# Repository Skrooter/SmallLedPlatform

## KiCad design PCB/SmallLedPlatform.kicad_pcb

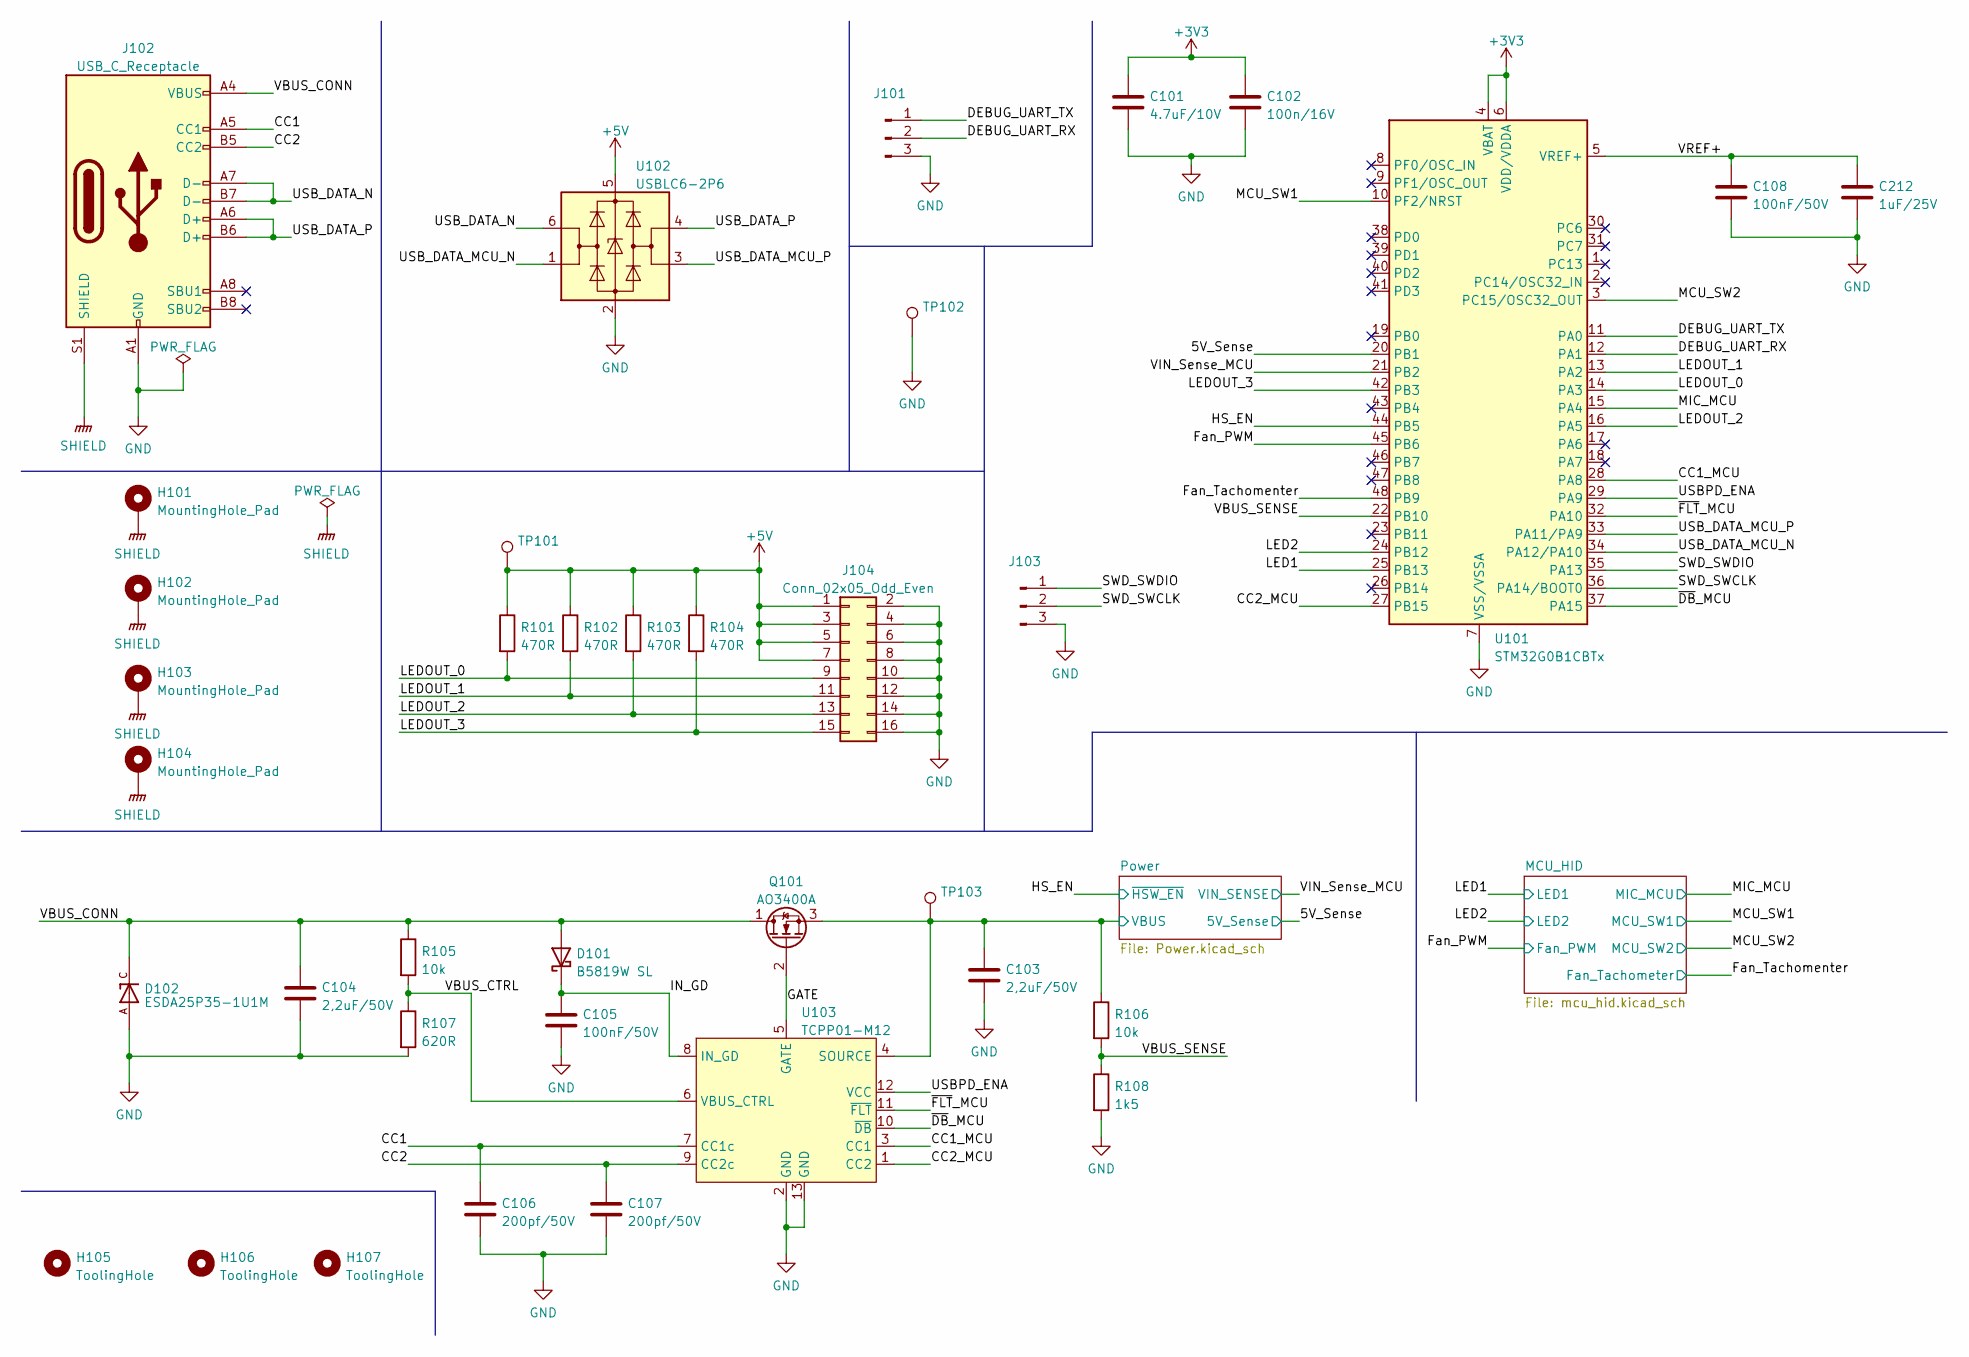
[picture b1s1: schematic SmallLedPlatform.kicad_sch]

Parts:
C101: 4.7uF/10V; C_0402_1005Metric; LCSC C23733
C102: 100n/16V; C_0402_1005Metric; LCSC C1525
C103, C104: 2,2uF/50V; C_0805_2012Metric; LCSC C49217
C105, C108: 100nF/50V; C_0402_1005Metric; LCSC C307331
C106, C107: 200pf/50V; C_0603_1608Metric; LCSC C1600
C212: 1uF/25V; C_0402_1005Metric; LCSC C52923
D101: B5819W SL; D_SOD-123; LCSC C8598
D102: ESDA25P35-1U1M; TVS_ESDA25P35-1U1M; PARTREV 2; LCSC C1974707
H101, H102, H103, H104: MountingHole_Pad; MountingHole_3.2mm_M3_Pad_Via
H105, H106, H107: ToolingHole; JLC_toolinghole
J101, J103: Conn_01x03_Male; PinHeader_1x03_P2.54mm_Vertical; LCSC C49257
J102: USB_C_Receptacle; USB_C_Receptacle_GCT_USB4105-xx-A_16P_TopMnt_Horizontal; LCSC C165948
J104: Conn_02x05_Odd_Even; PinHeader_2x08_P2.54mm_Horizontal; LCSC C68234
Q101: AO3400A; SOT-23; LCSC C20917
R101, R102, R103, R104: 470R; R_0402_1005Metric; LCSC C25117
R105, R106: 10k; R_0402_1005Metric; LCSC C25744
R107: 620R; R_0603_1608Metric; LCSC C23220
R108: 1k5; R_0402_1005Metric; LCSC C25867
TP101, TP102, TP103: TestPoint; TestPoint_Keystone_5000-5004_Miniature; LCSC C5199798
U101: STM32G0B1CBTx; LQFP-48_7x7mm_P0.5mm; LCSC C2847904
U102: USBLC6-2P6; SOT-666; LCSC C2827693
U103: TCPP01-M12; QFN-12-1EP_3x3mm_P0.5mm_EP1.6x1.6mm; LCSC C1121848

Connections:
+3V3: C101.1, C102.1, U101.4 (VBAT), U101.6 (VDD/VDDA); also elsewhere on the board
+5V: J104.1, J104.3, J104.5, J104.7, R101.1, R102.1, R103.1, R104.1, TP101.1, U102.5 (VBUS); also elsewhere on the board
/5V_Sense: U101.20 (PB1); also elsewhere on the board
/CC1: C106.1, J102.A5 (CC1), U103.7 (CC1c)
/CC1_MCU: U101.28 (PA8), U103.3 (CC1)
/CC2: C107.1, J102.B5 (CC2), U103.9 (CC2c)
/CC2_MCU: U101.27 (PB15), U103.1 (CC2)
/DEBUG_UART_RX: J101.2, U101.12 (PA1)
/DEBUG_UART_TX: J101.1, U101.11 (PA0)
/Fan_PWM: U101.45 (PB6); also elsewhere on the board
/Fan_Tachomenter: U101.48 (PB9); also elsewhere on the board
/GATE: Q101.2 (G), U103.5 (GATE)
/HS_EN: U101.44 (PB5); also elsewhere on the board
/IN_GD: C105.1, D101.1 (K), U103.8 (IN_GD)
/LED1: U101.25 (PB13); also elsewhere on the board
/LED2: U101.24 (PB12); also elsewhere on the board
/LEDOUT_0: J104.9, R101.2, U101.14 (PA3)
/LEDOUT_1: J104.11, R102.2, U101.13 (PA2)
/LEDOUT_2: J104.13, R103.2, U101.16 (PA5)
/LEDOUT_3: J104.15, R104.2, U101.42 (PB3)
/MCU_SW1: U101.10 (PF2/NRST); also elsewhere on the board
/MCU_SW2: U101.3 (PC15/OSC32_OUT); also elsewhere on the board
/MIC_MCU: U101.15 (PA4); also elsewhere on the board
/SWD_SWCLK: J103.2, U101.36 (PA14/BOOT0)
/SWD_SWDIO: J103.1, U101.35 (PA13)
/USBPD_ENA: U101.29 (PA9), U103.12 (VCC)
/USB_DATA_MCU_N: U101.34 (PA12/PA10), U102.1 (I/O1)
/USB_DATA_MCU_P: U101.33 (PA11/PA9), U102.3 (I/O2)
/USB_DATA_N: J102.A7 (D-), J102.B7 (D-), U102.6 (I/O1)
/USB_DATA_P: J102.A6 (D+), J102.B6 (D+), U102.4 (I/O2)
/VBUS_CONN: C104.1, D101.2 (A), D102.C, J102.A4 (VBUS), J102.A9 (VBUS), J102.B4 (VBUS), J102.B9 (VBUS), Q101.1 (D), R105.1
/VBUS_CTRL: R105.2, R107.1, U103.6 (VBUS_CTRL)
/VBUS_SENSE: R106.2, R108.1, U101.22 (PB10)
/VIN_Sense_MCU: U101.21 (PB2); also elsewhere on the board
/~DB_MCU: U101.37 (PA15), U103.10 (~DB)
/~FLT_MCU: U101.32 (PA10), U103.11 (~FLT)
GND: C101.2, C102.2, C103.2, C104.2, C105.2, C106.2, C107.2, C108.2, C212.2, D102.A, J101.3, J102.A1 (GND), J102.A12 (GND), J102.B1 (GND), J102.B12 (GND), J103.3, J104.2, J104.4, J104.6, J104.8, J104.10, J104.12, J104.14, J104.16, R107.2, R108.2, TP102.1, U101.7 (VSS/VSSA), U102.2 (GND), U103.2 (GND), U103.13 (GND); also elsewhere on the board
IN: C103.1, Q101.3 (S), R106.1, TP103.1, U103.4 (SOURCE); also elsewhere on the board
SHIELD: H101.1, H102.1, H103.1, H104.1, J102.S1 (SHIELD)

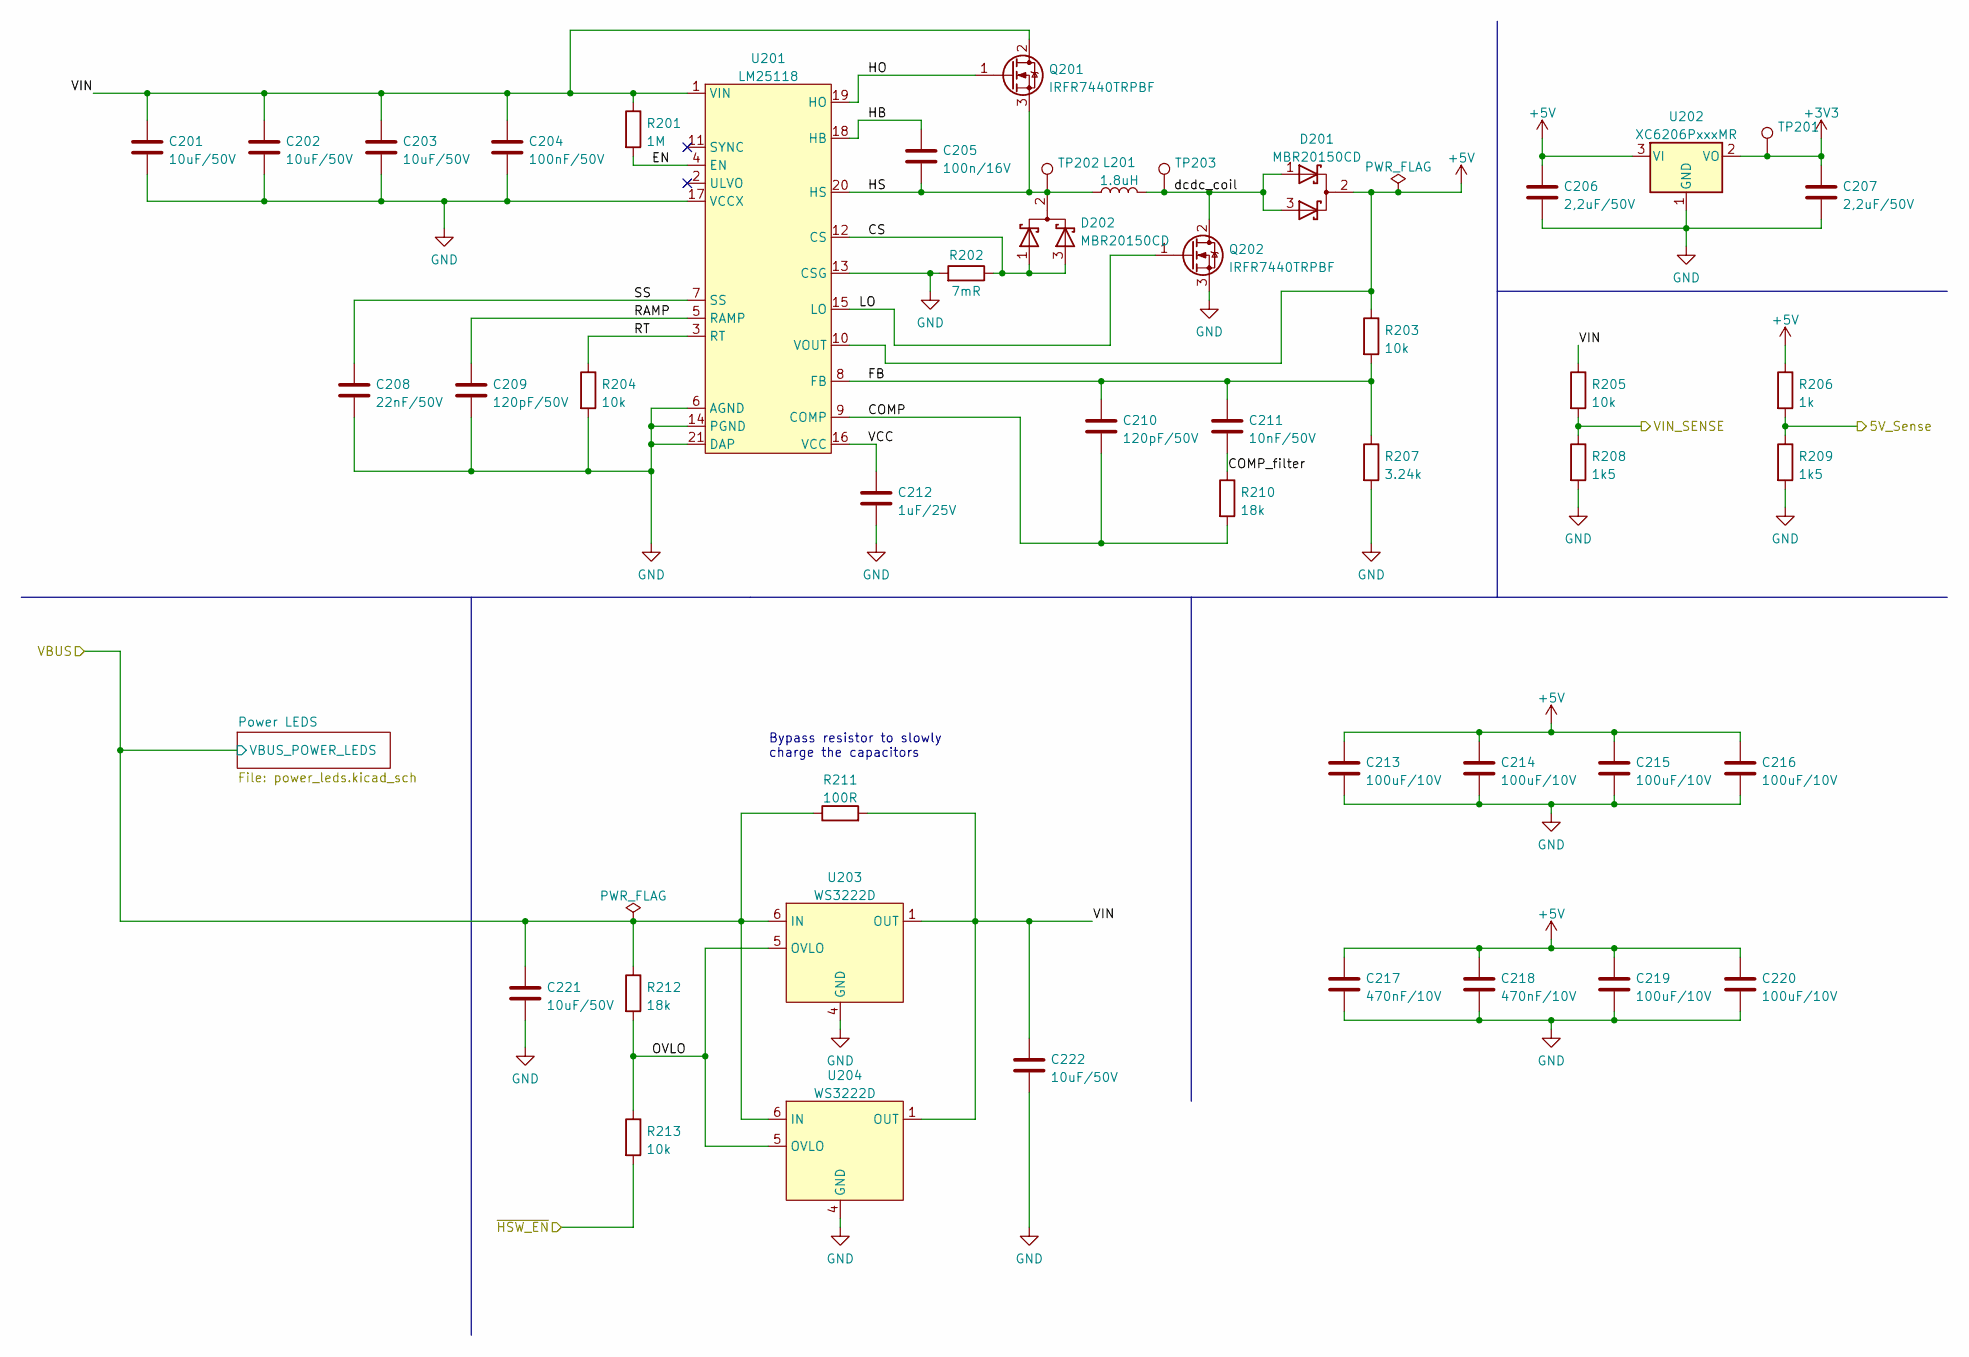
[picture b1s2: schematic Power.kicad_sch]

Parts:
C201, C202, C203, C221, C222: 10uF/50V; C_0805_2012Metric; LCSC C440198
C204: 100nF/50V; C_0402_1005Metric; LCSC C307331
C205: 100n/16V; C_0402_1005Metric; LCSC C1525
C206, C207: 2,2uF/50V; C_0805_2012Metric; LCSC C49217
C208: 22nF/50V; C_0402_1005Metric; LCSC C1532
C209, C210: 120pF/50V; C_0402_1005Metric; LCSC C312114
C211: 10nF/50V; C_0402_1005Metric; LCSC C15195
C212: 1uF/25V; C_0402_1005Metric; LCSC C52923
C213, C214, C215, C216, C219, C220: 100uF/10V; C_1206_3216Metric; LCSC C312983
C217, C218: 470nF/10V; C_0402_1005Metric; LCSC C47339
D201, D202: MBR20150CD; TO-252-2; LCSC C698783
L201: 1.8uH; L_12x12mm_H8mm; LCSC C718301
Q201, Q202: IRFR7440TRPBF; TO-252-2; LCSC C97244
R201: 1M; R_0402_1005Metric; LCSC C26083
R202: 7mR; R_2512_6332Metric; LCSC C728341
R203, R204, R205, R213: 10k; R_0402_1005Metric; LCSC C25744
R206: 1k; R_0402_1005Metric; LCSC C11702
R207: 3.24k; R_0402_1005Metric; LCSC C25890
R208, R209: 1k5; R_0402_1005Metric; LCSC C25867
R210, R212: 18k; R_0402_1005Metric; LCSC C25762
R211: 100R; R_1206_3216Metric; LCSC C17901
TP201, TP202, TP203: TestPoint; TestPoint_Keystone_5000-5004_Miniature; LCSC C5199798
U201: LM25118; HTSSOP-20-1EP_4.4x6.5mm_P0.65mm_EP3.4x6.5mm_Mask2.75x3.43mm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; LCSC C470962
U202: XC6206PxxxMR; SOT-23-3; LCSC C5446
U203, U204: WS3222D; WDFN-8-1EP_2x2mm_P0.5mm_EP0.8x1.2mm; LCSC C239703

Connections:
+3V3: C207.1, TP201.1, U202.2 (VO); also elsewhere on the board
+5V: C206.1, C213.1, C214.1, C215.1, C216.1, C217.1, C218.1, C219.1, C220.1, D201.2 (A), R203.1, R206.1, U201.10 (VOUT), U202.3 (VI); also elsewhere on the board
/5V_Sense: R206.2, R209.1; also elsewhere on the board
/HS_EN: R213.2; also elsewhere on the board
/Power/COMP: C210.2, R210.2, U201.9 (COMP)
/Power/COMP_filter: C211.2, R210.1
/Power/CS: D202.1 (K), D202.3 (K), R202.1, U201.12 (CS)
/Power/EN: R201.2, U201.4 (EN)
/Power/FB: C210.1, C211.1, R203.2, R207.1, U201.8 (FB)
/Power/HB: C205.1, U201.18 (HB)
/Power/HO: Q201.1 (G), U201.19 (HO)
/Power/HS: C205.2, D202.2 (A), L201.1, Q201.3 (S), TP202.1, U201.20 (HS)
/Power/LO: Q202.1 (G), U201.15 (LO)
/Power/OVLO: R212.2, R213.1, U203.5 (OVLO), U204.5 (OVLO)
/Power/RAMP: C209.1, U201.5 (RAMP)
/Power/RT: R204.1, U201.3 (RT)
/Power/SS: C208.1, U201.7 (SS)
/Power/VIN: C201.1, C202.1, C203.1, C204.1, C222.1, Q201.2 (D), R201.1, R205.1, R211.2, U201.1 (VIN), U203.1 (OUT), U203.2 (OUT), U203.3 (OUT), U204.1 (OUT), U204.2 (OUT), U204.3 (OUT)
/Power/dcdc_coil: D201.1 (K), D201.3 (K), L201.2, Q202.2 (D), TP203.1
/VIN_Sense_MCU: R205.2, R208.1; also elsewhere on the board
GND: C201.2, C202.2, C203.2, C204.2, C206.2, C207.2, C208.2, C209.2, C212.2, C213.2, C214.2, C215.2, C216.2, C217.2, C218.2, C219.2, C220.2, C221.2, C222.2, Q202.3 (S), R202.2, R204.2, R207.2, R208.2, R209.2, U201.6 (AGND), U201.13 (CSG), U201.14 (PGND), U201.17 (VCCX), U201.21 (DAP), U202.1 (GND), U203.4 (GND), U203.9 (GND), U204.4 (GND), U204.9 (GND); also elsewhere on the board
IN: C221.1, R211.1, R212.1, U203.6 (IN), U203.7 (IN), U203.8 (IN), U204.6 (IN), U204.7 (IN), U204.8 (IN); also elsewhere on the board

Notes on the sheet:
Bypass resistor to slowly charge the capacitors

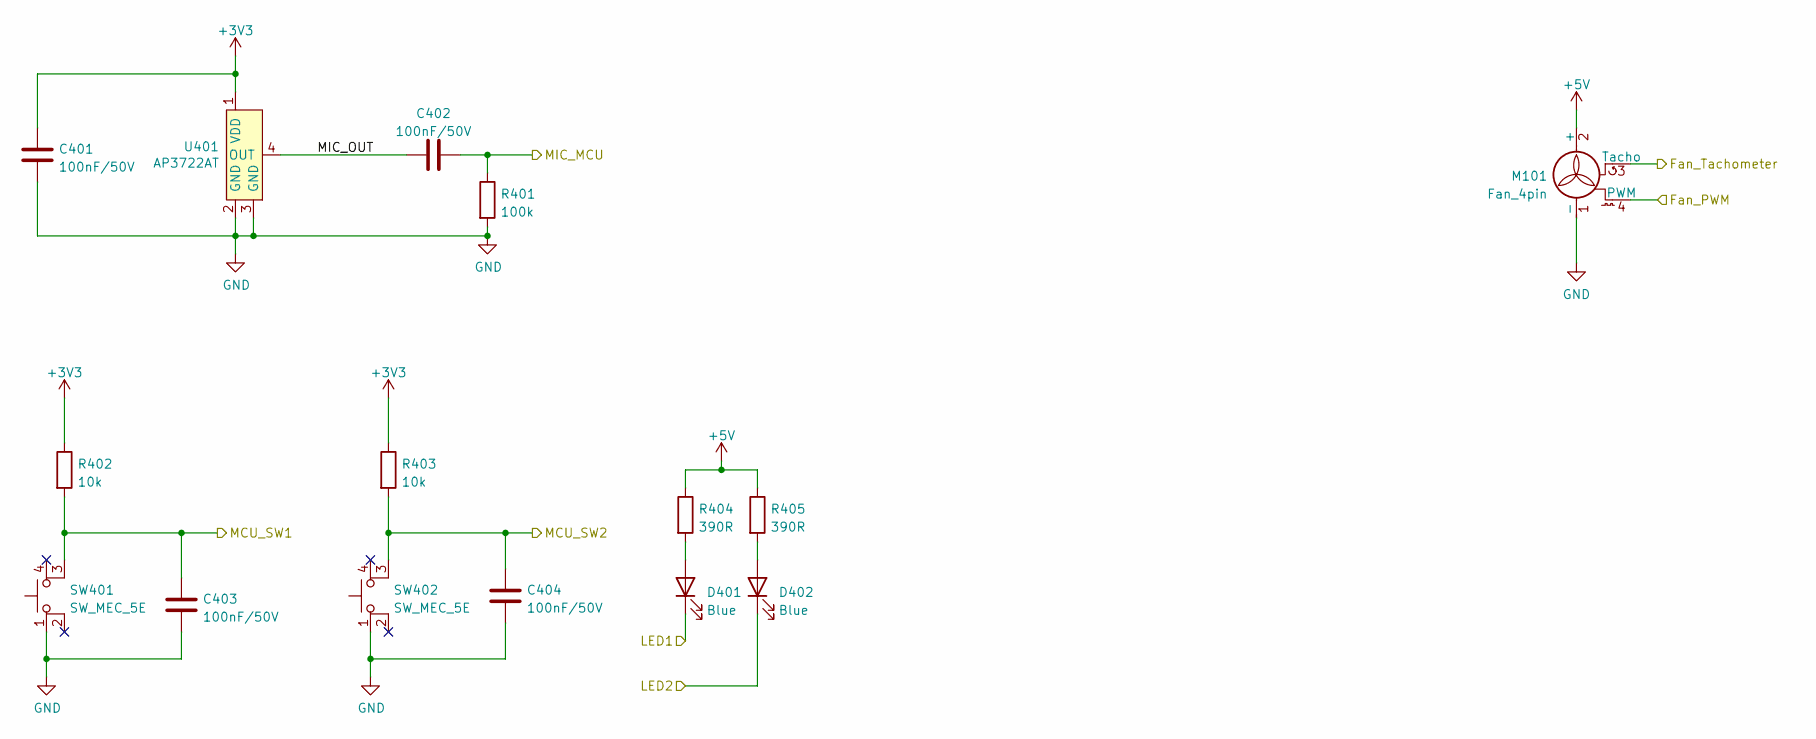
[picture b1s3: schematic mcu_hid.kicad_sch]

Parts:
C401, C402, C403, C404: 100nF/50V; C_0402_1005Metric; LCSC C307331
D401, D402: Blue; LED_0603_1608Metric; LCSC C72041
M101: Fan_4pin; PinHeader_1x04_P2.54mm_Vertical_SMD_Pin1Left
R401: 100k; R_0402_1005Metric; LCSC C25741
R402, R403: 10k; R_0402_1005Metric; LCSC C25744
R404, R405: 390R; R_0603_1608Metric; LCSC C23151
SW401, SW402: SW_MEC_5E; SW_MEC_5GSH9
U401: AP3722AT; LCSC C918198

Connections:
+3V3: C401.1, R402.1, R403.1, U401.1 (VDD); also elsewhere on the board
+5V: R404.1, R405.1; also elsewhere on the board
/LED1: D401.1 (K); also elsewhere on the board
/LED2: D402.1 (K); also elsewhere on the board
/MCU_HID/MIC_OUT: C402.1, U401.4 (OUT)
/MCU_SW1: C403.1, R402.2, SW401.3 (K); also elsewhere on the board
/MCU_SW2: C404.1, R403.2, SW402.3 (K); also elsewhere on the board
/MIC_MCU: C402.2, R401.1; also elsewhere on the board
GND: C401.2, C403.2, C404.2, R401.2, SW401.1, SW402.1, U401.2 (GND), U401.3 (GND); also elsewhere on the board
unnamed: D401.2 (A), R404.2
unnamed: D402.2 (A), R405.2

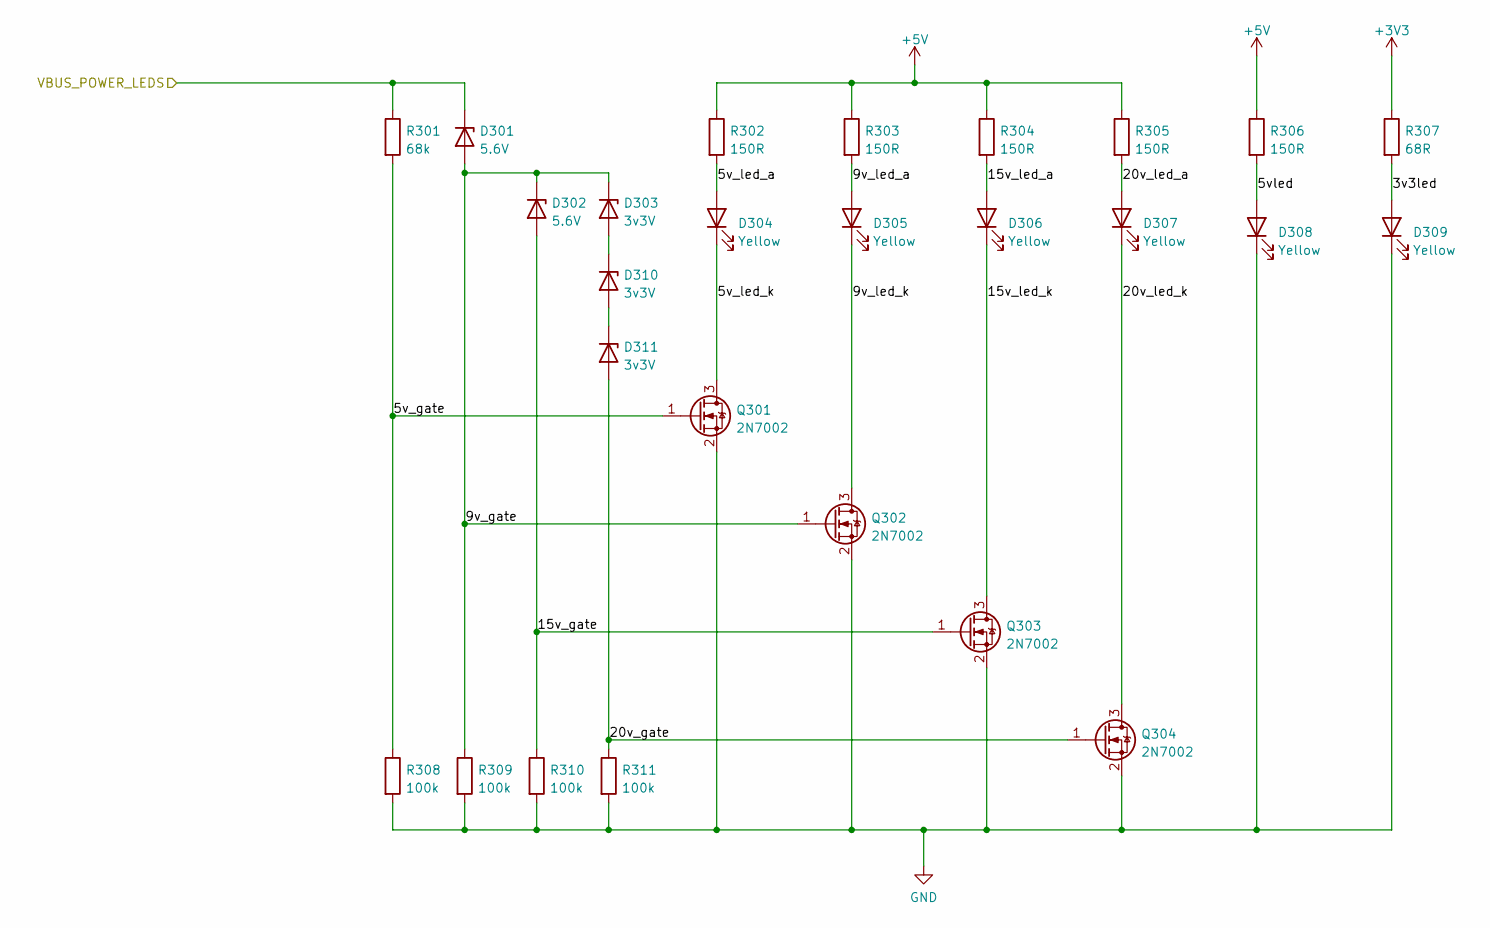
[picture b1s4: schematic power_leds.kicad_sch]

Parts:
D301, D302: 5.6V; D_MiniMELF; LCSC C8062
D303, D310, D311: 3v3V; D_MiniMELF; LCSC C8056
D304, D305, D306, D307, D308, D309: Yellow; LED_0603_1608Metric_smaller_silk; LCSC C72038
Q301, Q302, Q303, Q304: 2N7002; SOT-23; LCSC C8545
R301: 68k; R_0402_1005Metric; LCSC C36871
R302, R303, R304, R305, R306: 150R; R_0402_1005Metric; LCSC C25082
R307: 68R; R_0603_1608Metric; LCSC C27592
R308, R309, R310, R311: 100k; R_0402_1005Metric; LCSC C25741

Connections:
+3V3: R307.1; also elsewhere on the board
+5V: R302.1, R303.1, R304.1, R305.1, R306.1; also elsewhere on the board
/Power/Power LEDS/3v3led: D309.2 (A), R307.2
/Power/Power LEDS/5v_gate: Q301.1 (G), R301.2, R308.1
/Power/Power LEDS/5v_led_a: D304.2 (A), R302.2
/Power/Power LEDS/5v_led_k: D304.1 (K), Q301.3 (D)
/Power/Power LEDS/5vled: D308.2 (A), R306.2
/Power/Power LEDS/9v_gate: D301.2 (A), D302.1 (K), D303.1 (K), Q302.1 (G), R309.1
/Power/Power LEDS/9v_led_a: D305.2 (A), R303.2
/Power/Power LEDS/9v_led_k: D305.1 (K), Q302.3 (D)
/Power/Power LEDS/15v_gate: D302.2 (A), Q303.1 (G), R310.1
/Power/Power LEDS/15v_led_a: D306.2 (A), R304.2
/Power/Power LEDS/15v_led_k: D306.1 (K), Q303.3 (D)
/Power/Power LEDS/20v_gate: D311.2 (A), Q304.1 (G), R311.1
/Power/Power LEDS/20v_led_a: D307.2 (A), R305.2
/Power/Power LEDS/20v_led_k: D307.1 (K), Q304.3 (D)
GND: D308.1 (K), D309.1 (K), Q301.2 (S), Q302.2 (S), Q303.2 (S), Q304.2 (S), R308.2, R309.2, R310.2, R311.2; also elsewhere on the board
IN: D301.1 (K), R301.1; also elsewhere on the board
unnamed: D303.2 (A), D310.1 (K)
unnamed: D310.2 (A), D311.1 (K)

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
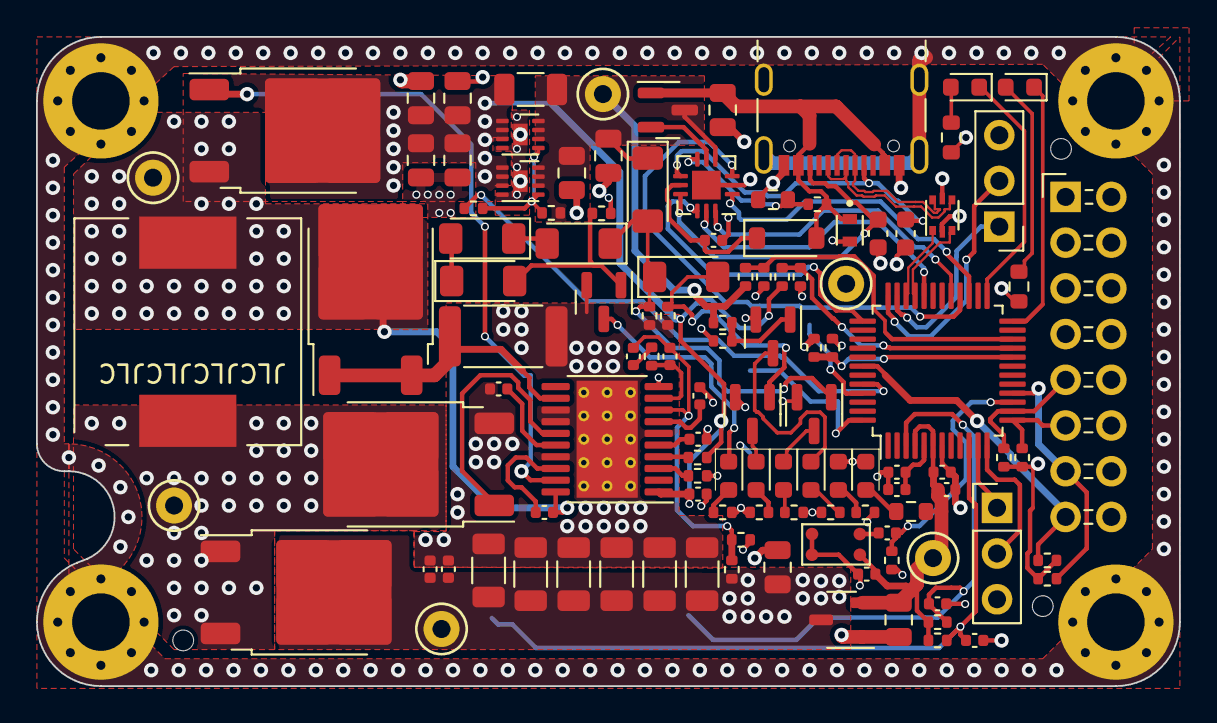
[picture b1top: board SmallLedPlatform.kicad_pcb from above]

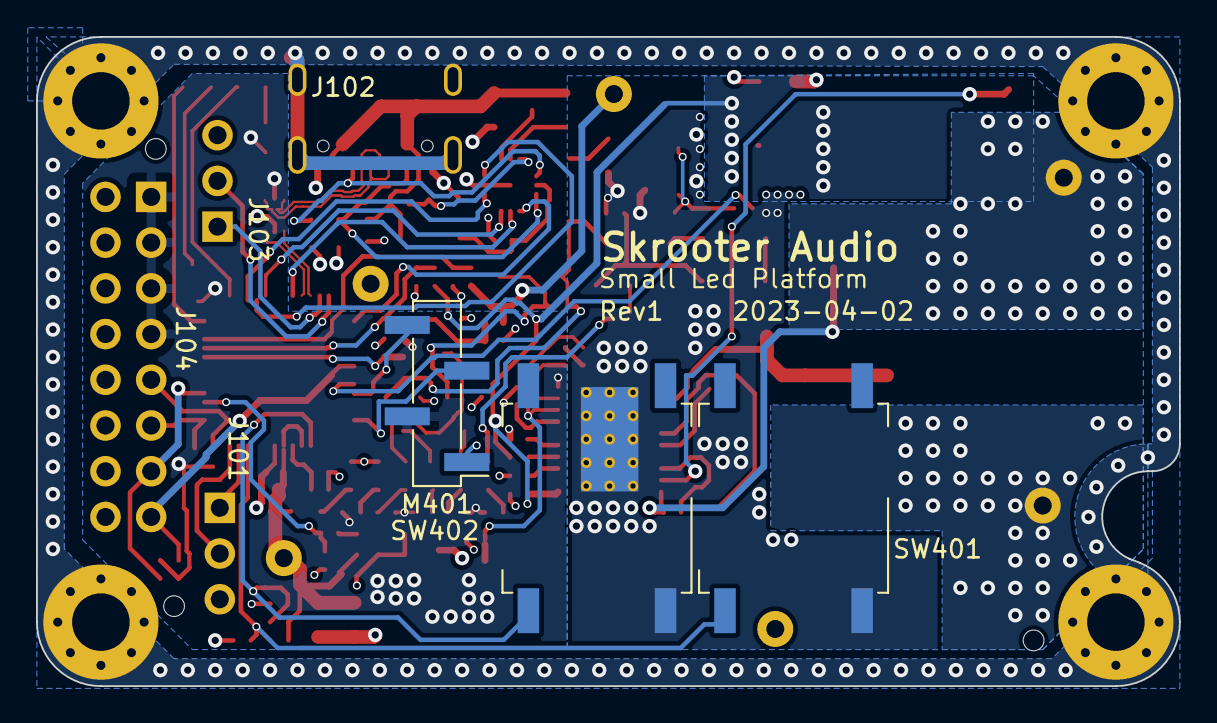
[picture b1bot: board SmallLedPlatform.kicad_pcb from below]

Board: 4 copper layers, 63.5 x 36.1 mm, 125 parts (3 on the bottom side), 75 nets.

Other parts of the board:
C109: 1uF/25V; C_0402_1005Metric
M401: Fan_4pin; PinHeader_1x04_P2.54mm_Vertical_SMD_Pin1Left

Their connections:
+5V: M401.2 (+); also elsewhere on the board
/Fan_PWM: M401.4 (PWM); also elsewhere on the board
/Fan_Tachomenter: M401.3 (Tacho); also elsewhere on the board
GND: C109.2, M401.1 (-); also elsewhere on the board

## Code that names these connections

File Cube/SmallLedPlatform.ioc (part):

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Mcu.Name=STM32G0B1C(B-C-E)Tx
Mcu.Package=LQFP48
Mcu.UserName=STM32G0B1CBTx
PA0.Mode=Asynchronous
PA0.Signal=USART4_TX
PA1.Mode=Asynchronous
PA1.Signal=USART4_RX
PA10.GPIOParameters=GPIO_Label
PA10.GPIO_Label=FLT_MCU
PA10.Signal=GPIO_Output
PA11\ [PA9].Mode=Device
PA11\ [PA9].Signal=USB_DM
PA12\ [PA10].Mode=Device
PA12\ [PA10].Signal=USB_DP
PA13.Mode=Serial_Wire
PA13.Signal=SYS_SWDIO
PA14-BOOT0.Mode=Serial_Wire
PA14-BOOT0.Signal=SYS_SWCLK
PA15.GPIOParameters=GPIO_Label
PA15.GPIO_Label=DB_MCU
PA15.Signal=GPIO_Output
PA2.GPIOParameters=GPIO_Label
PA2.GPIO_Label=LEDOUT_1
PA2.Signal=S_TIM2_CH3
PA3.GPIOParameters=GPIO_Label
PA3.GPIO_Label=LEDOUT_0
PA3.Signal=S_TIM2_CH4
PA4.GPIOParameters=GPIO_Label
PA4.GPIO_Label=MICIN
PA4.Mode=IN4
PA4.Signal=ADC1_IN4
PA5.GPIOParameters=GPIO_Label
PA5.GPIO_Label=LEDOUT_2
PA5.Signal=S_TIM2_CH1_ETR
PA6.GPIOParameters=GPIO_Label
PA6.GPIO_Label=sense_vbus
PA6.Mode=IN6
PA6.Signal=ADC1_IN6
PA8.Mode=Sink_AllSignals
PA8.Signal=UCPD1_CC1
PA9.GPIOParameters=GPIO_Label
PA9.GPIO_Label=USBPD_ENA
PA9.Signal=GPIO_Output
PB1.GPIOParameters=GPIO_Label
PB1.GPIO_Label=sense_5v
PB1.Mode=IN9
PB1.Signal=ADC1_IN9
PB10.GPIOParameters=GPIO_Label
PB10.GPIO_Label=sense_vbus
PB10.Mode=IN11
PB10.Signal=ADC1_IN11
PB12.GPIOParameters=GPIO_Label
PB12.GPIO_Label=MCU_LED2
PB12.Signal=GPIO_Output
PB13.GPIOParameters=GPIO_Label
PB13.GPIO_Label=MCU_LED1
PB13.Signal=GPIO_Output
PB15.Mode=Sink_AllSignals
PB15.Signal=UCPD1_CC2
PB2.GPIOParameters=GPIO_Label
PB2.GPIO_Label=sense_vin
PB2.Mode=IN10
PB2.Signal=ADC1_IN10
PB3.GPIOParameters=GPIO_Label
PB3.GPIO_Label=LEDOUT_3
PB3.Signal=S_TIM2_CH2
PB5.GPIOParameters=GPIO_Label
PB5.GPIO_Label=HS_EN
PB5.Signal=GPIO_Output
PB6.GPIOParameters=GPIO_Label
PB6.GPIO_Label=FAN_PWM
PB6.Signal=S_TIM4_CH1
PB9.GPIOParameters=GPIO_Label
PB9.GPIO_Label=FAN_TACH
PB9.Signal=S_TIM4_CH4
PC15-OSC32_OUT\ (PC15).GPIOParameters=GPIO_Label
PC15-OSC32_OUT\ (PC15).GPIO_Label=sw2
PC15-OSC32_OUT\ (PC15).Signal=GPIO_Input
PF2-NRST.GPIOParameters=GPIO_Label
PF2-NRST.GPIO_Label=sw1
PF2-NRST.Signal=GPIO_Input
RCC.HSE_VALUE=8000000
RCC.SYSCLKFreq_VALUE=64000000
RCC.SYSCLKSource=RCC_SYSCLKSOURCE_PLLCLK
board=custom

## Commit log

2023-01-16 Add a new DC/DC solution to the schematic
    Components has been added to layout, but not properly done
2023-01-21 reroute pretty much everything
    Routing is done for new DC/DC!
2023-01-23 Add LEDs for each USBPD level and a microphone
2023-02-07 Prepare board for manufactoring
2023-02-07 Add fan header on backside of board
2023-02-10 Added hole for fan cable entry
2023-02-10 Fix DRC and outline
2023-02-11 Add production text to PCB
2023-03-01 Remove duplicate file
2023-03-11 Fix review comments
2023-03-14 Update Cube project
2023-04-14 Final fixes before production
